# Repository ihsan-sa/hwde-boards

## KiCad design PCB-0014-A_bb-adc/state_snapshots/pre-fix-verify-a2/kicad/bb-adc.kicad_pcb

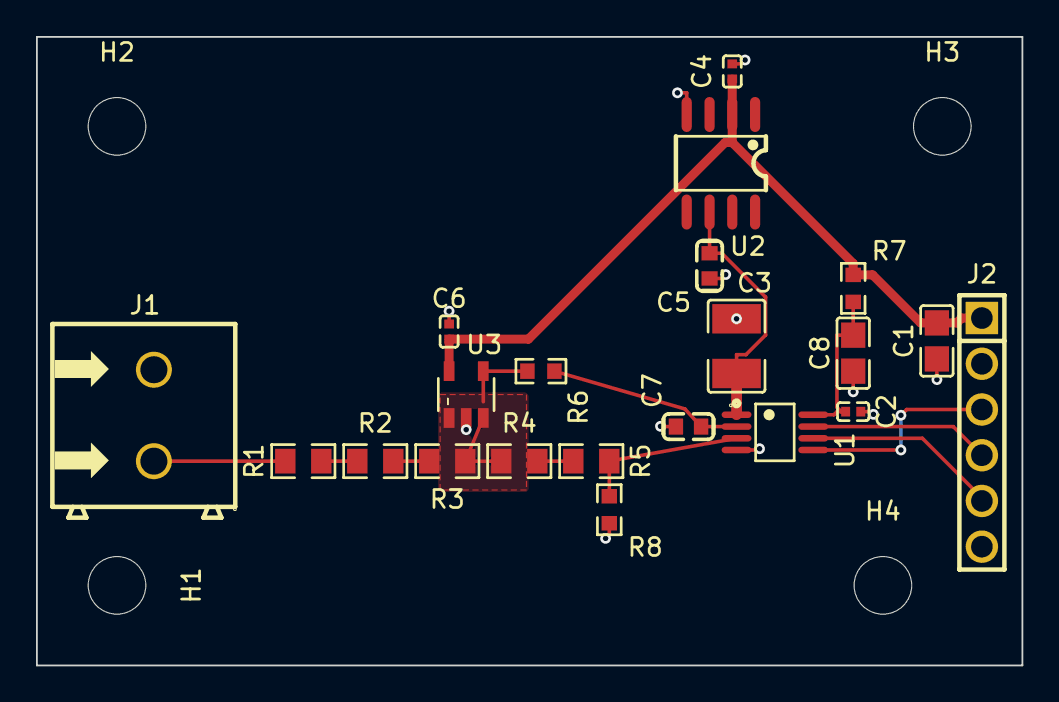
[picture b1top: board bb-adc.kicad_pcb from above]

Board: 2 copper layers, 54.8 x 34.9 mm, 25 parts (0 on the bottom side), 15 nets.

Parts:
C1, C8: 10uF 25V X5R; C0805
C2, C4, C6: 100nF 16V X7R; C0402
C3: 47uF 16V X7R; C1210
C5: 2.2uF 10V X7R; C0603
C7: 1nF 50V C0G/NP0; C0603
H1, H2, H3, H4: M3_3.2mm; MountingHole_3.2mm_M3
J1: WJ500V-5.08-2P; CONN-TH_2P-P5.00_WJ500V-5.08-2P
J2: 1x6P 2.54mm male header; HDR-TH_6P-P2.54-V-M-1
R1, R2, R3, R4, R5: 200K 0.02% 10ppm/C; R0805
R6: 49.9 ohm 1%; R0603
R7: 10 ohm 1%; R0603
R8: 0 ohm 1%; R0603
U1: ADS8326IB; VSSOP-8_L3.0-W3.0-P0.65-LS5.0-BL
U2: ADR4520B; SOIC-8_L5.0-W4.0-P1.27-LS6.0-BL
U3: OPA320; SOT-23-5_L3.0-W1.7-P0.95-LS2.8-BR

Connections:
+3V3: C1.1, C4.1, C6.1, J2.1, R7.1, U2.2, U3.5
/AGND_SENSE: R5.2, R8.1, U1.3
/AIN_ADC: C7.1, R6.2, U1.2
/AIN_BUF: R6.1, U3.1, U3.4
/AIN_DIV: R3.2, R4.1, U3.3
/AIN_RAW: J1.1, R1.1
/ATT_A: R1.2, R2.1
/ATT_B: R2.2, R3.1
/ATT_C: R4.2, R5.1
/CS: J2.3, U1.5
/DOUT: J2.5, U1.6
/SCLK: J2.4, U1.7
GND: C1.2, C2.2, C3.2, C4.2, C5.2, C6.2, C7.2, C8.2, J1.2, J2.2, J2.6, R8.2, U1.4, U2.4, U3.2
VDD_ADC: C2.1, C8.1, R7.2, U1.8
VREF: C3.1, C5.1, U1.1, U2.6

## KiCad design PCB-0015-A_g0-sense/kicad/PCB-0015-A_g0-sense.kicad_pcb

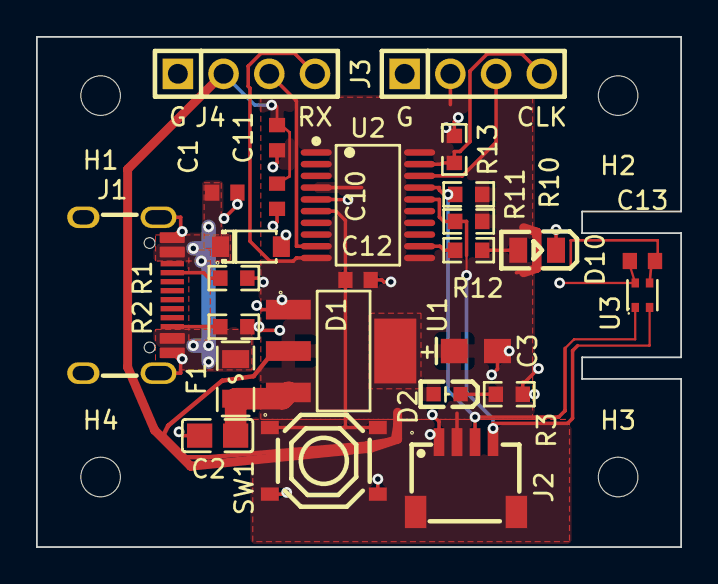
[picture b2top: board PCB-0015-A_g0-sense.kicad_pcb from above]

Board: 2 copper layers, 35.8 x 28.3 mm, 30 parts (0 on the bottom side), 16 nets.

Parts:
C1, C10, C12, C13: 100nF 50V X7R; C0603
C2: 10uF 25V X5R; C0805
C3: 22uF 10V tantalum; CASE-A_3216
C11: 4.7uF 16V X5R; C0603
D1: SMF5.0A TVS 5V; SOD-123_L2.8-W1.8-LS3.7-RD
D2: Red LED; LED-SMD_L1.6-W0.8-R-RD
D10: Green 0805; LED0805-R-RD
F1: PTC 750mA 16V; F0805
H1, H2, H3, H4: MountingHole_2.2mm_M2
J1: TYPE-C-31-M-12; USB-C_SMD-TYPE-C-31-M-12_1
J2: Qwiic JST SH 4P; CONN-SMD_4P-P1.00_SM04B-SRSS-TB-LF-SN
J3, J4: 1x4 2.54mm THT (DNP); HDR-TH_4P-P2.54-V-M
R1, R2: 5.1k 1%; R0603
R3: 680R 1%; R0603
R10, R11: 1.5k; R0603
R12: 100R; R0603
R13: 10k; R0603
SW1: Tactile button; SW-SMD_4P-L5.1-W5.1-P3.70-LS6.5-TL_H1.5
U1: AMS1117-3.3; SOT-223-3_L6.5-W3.4-P2.30-LS7.0-BR
U2: STM32G030F6P6; TSSOP-20_L6.5-W4.4-P0.65-LS6.4-BL
U3: SHT40-AD1B-R2; DFN-4_L1.5-W1.5-P0.8-TL-EP

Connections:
+3V3: C3.1, C10.1, C11.1, C13.1, D2.1, J2.2, J3.2, J4.2, R10.2, R11.2, U1.2, U1.4, U2.4, U3.3
+5V: C2.1, F1.2, U1.3
/main/LED_A: D10.1, R12.2
/main/LED_USER: R12.1, U2.12
/main/NRST: C12.1, SW1.1, SW1.2, U2.6
/main/SCL: J2.4, R11.1, U2.16, U3.2
/main/SDA: J2.3, R10.1, U2.17, U3.1
/main/SWCLK: J3.4, R13.1, U2.19
/main/SWDIO: J3.3, U2.18
/main/UART_RX: J4.4, U2.10
/main/UART_TX: J4.3, U2.9
/power/CC1: J1.A5, R1.1
/power/CC2: J1.B5, R2.1
/power/PWR_LED_K: D2.2, R3.1
GND: C1.2, C2.2, C3.2, C10.2, C11.2, C12.2, C13.2, D1.2, D10.2, J1.1, J1.2, J1.3, J1.4, J1.A1B12, J1.B1A12, J2.1, J3.1, J4.1, R1.2, R2.2, R3.2, R13.2, SW1.3, SW1.4, U1.1, U2.5, U3.4
VBUS: C1.1, D1.1, F1.1, J1.A4B9, J1.B4A9
